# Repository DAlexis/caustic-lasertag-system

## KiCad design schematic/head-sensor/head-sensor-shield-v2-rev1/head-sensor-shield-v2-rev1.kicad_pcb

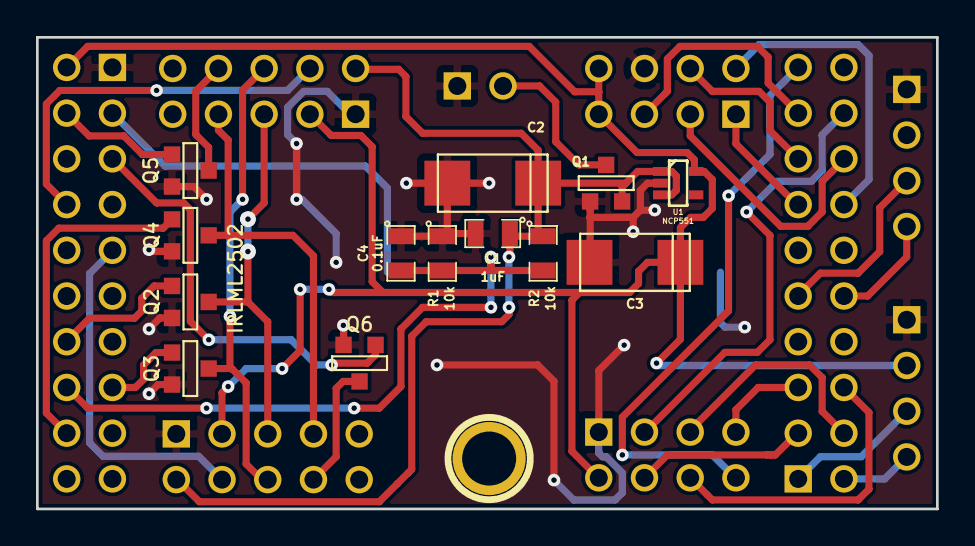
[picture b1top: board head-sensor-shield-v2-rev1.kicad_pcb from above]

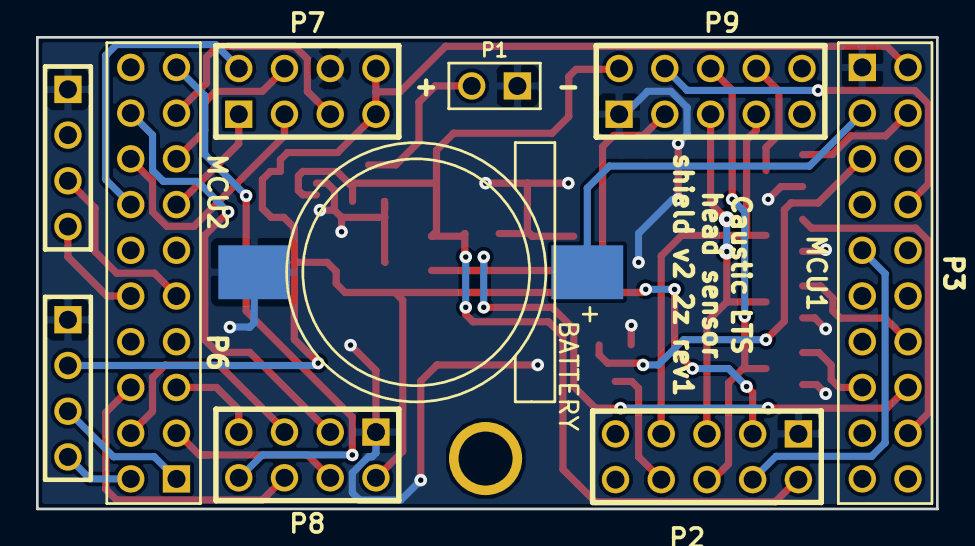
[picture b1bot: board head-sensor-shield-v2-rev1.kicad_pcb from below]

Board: 2 copper layers, 50.0 x 26.2 mm, 23 parts (10 on the bottom side), 33 nets.

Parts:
+: BATTERY; CR1220-smd
C1: 1uF; SM0805
C2, C3: 100uF; c_tant_C
C4: 0.1uF; SM0805
P1: Power_in; PIN_ARRAY_2X1
P2: Zone2; PIN_ARRAY_5x2
P3: MCU1; pin_array_10x2
P4: UART1; PIN_ARRAY_4x1
P5: UART3; PIN_ARRAY_4x1
P6: MCU2; pin_array_10x2
P7: RFID; pin_array_4x2
P8: NRF24L01; pin_array_4x2
P9: Zone1; PIN_ARRAY_5x2
Q1, Q2, Q3, Q4, Q6: SOT23GDS
Q5: IRLML2502; SOT23GDS
R1, R2: 10k; SM0805
U1: NCP551; sot323-5-fx

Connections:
+3.3V: C3.1, P2.3, P3.2, P5.2, P7.7, P7.8, P8.2, P9.3, U1.5
+BATT: +.1, P3.3
GND: +.2, C1.2, C2.2, C3.2, C4.1, P1.1, P2.1, P3.1, P4.1, P5.1, P7.6, P8.1, P9.1, Q1.G, Q2.S, Q3.S, Q4.S, Q5.S, Q6.S, R1.1, U1.2
unnamed: P3.18, Q4.G
unnamed: P3.15, Q3.G
unnamed: P3.5, Q6.G
unnamed: P5.4, P6.2
unnamed: P2.7, P9.7, Q4.D
unnamed: P3.14, Q2.G
unnamed: P1.2, Q1.D
unnamed: P6.19, P8.8
unnamed: P6.18, P8.3
unnamed: P6.3, P8.4
unnamed: P6.4, P8.5
unnamed: P6.6, P8.6
unnamed: P6.5, P8.7
unnamed: P6.13, P7.1
unnamed: P5.3, P6.1
unnamed: P2.8, Q6.D
unnamed: C4.2, P3.16, R1.2, R2.2
unnamed: P2.4, P3.9
unnamed: P3.8, P9.4
unnamed: P4.4, P6.10
unnamed: P4.3, P6.9
unnamed: P3.4, Q5.G
unnamed: P9.8, Q5.D
unnamed: P2.5, P9.5, Q2.D
unnamed: P2.6, P9.6, Q3.D
unnamed: P6.14, P7.2
unnamed: P6.17, P7.5
unnamed: P6.16, P7.3
unnamed: P6.15, P7.4
VCC: C1.1, C2.1, P2.2, P9.2, Q1.S, R2.1, U1.1, U1.3

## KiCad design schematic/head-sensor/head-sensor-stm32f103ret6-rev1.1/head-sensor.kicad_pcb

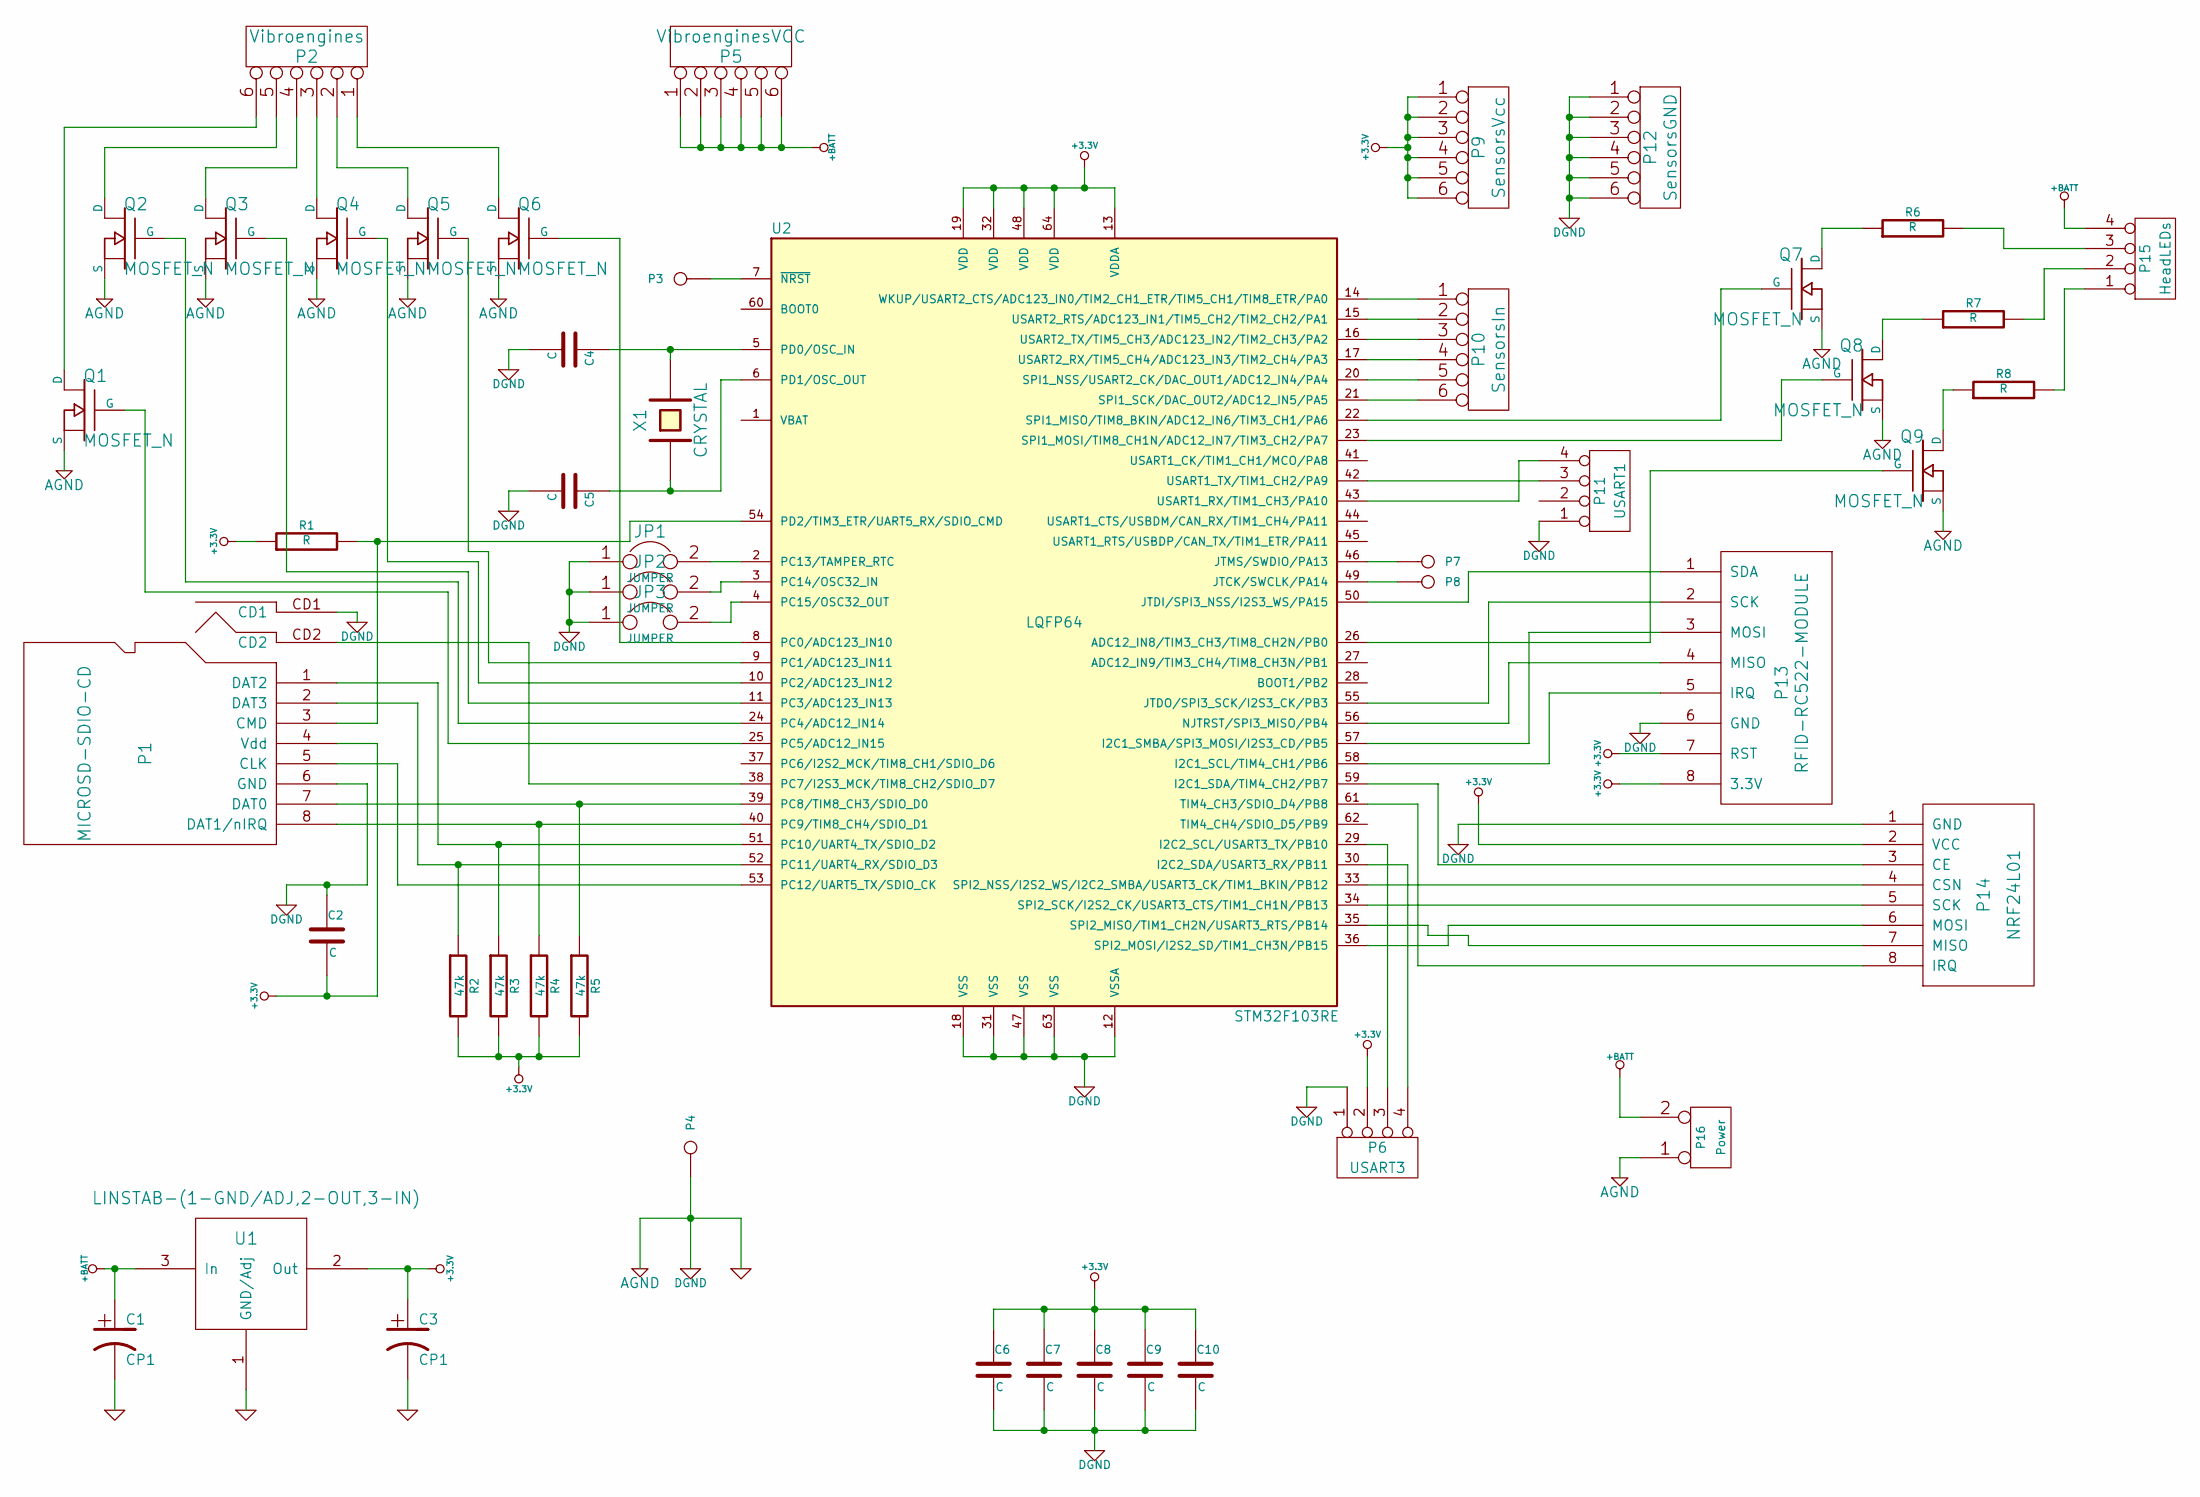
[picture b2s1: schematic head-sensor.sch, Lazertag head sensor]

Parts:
C1, C3: CP1
C2, C4, C5, C6, C7, C8, C9, C10: C
JP1, JP2, JP3: JUMPER
P1: MICROSD-SDIO-CD
P2: Vibroengines
P3: NRST
P4: SWGND
P5: VibroenginesVCC
P6: USART3
P7: SWDIO
P8: SWCLK
P9: SensorsVcc
P10: SensorsIn
P11: USART1
P12: SensorsGND
P13: RFID-RC522-MODULE
P14: NRF24L01
P15: HeadLEDs
P16: Power
Q1, Q2, Q3, Q4, Q5, Q6, Q7, Q8, Q9: MOSFET_N
R1, R6, R7, R8: R
R2, R3, R4, R5: 47k
U1: LINSTAB-(1-GND/ADJ,2-OUT,3-IN)
U2: STM32F103RE; LQFP64
X1: CRYSTAL

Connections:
+3.3V: C2.2, C3.1, C6.1, C7.1, C8.1, C9.1, C10.1, P1.4 (Vdd), P6.2, P9.1, P9.2, P9.3, P9.4, P9.5, P9.6, P13.7 (RST), P13.8 (3.3V), P14.2 (VCC), R1.1, R2.2, R3.2, R4.2, R5.2, U1.2 (Out), U2.13 (VDDA), U2.19 (VDD), U2.32 (VDD), U2.48 (VDD), U2.64 (VDD)
+BATT: C1.1, P5.1, P5.2, P5.3, P5.4, P5.5, P5.6, P15.4, P16.2 (PM), U1.3 (In)
AGND: C1.2, C2.1, C3.2, C4.2, C5.2, C6.2, C7.2, C8.2, C9.2, C10.2, JP1.1, JP2.1, JP3.1, P1.6 (GND), P1.CD1, P4.1, P6.1, P11.1, P12.1, P12.2, P12.3, P12.4, P12.5, P12.6, P13.6 (GND), P14.1 (GND), P16.1, Q1.S, Q2.S, Q3.S, Q4.S, Q5.S, Q6.S, Q7.S, Q8.S, Q9.S, U1.1 (GND/Adj), U2.12 (VSSA), U2.18 (VSS), U2.31 (VSS), U2.47 (VSS), U2.63 (VSS)
unnamed: Q8.D, R7.1
unnamed: Q7.D, R6.1
unnamed: P15.2, R7.2
unnamed: P15.3, R6.2
unnamed: P2.6, Q1.D
unnamed: P1.8 (DAT1/nIRQ), R4.1, U2.40 (PC9/TIM8_CH4/SDIO_D1)
unnamed: P1.7 (DAT0), R5.1, U2.39 (PC8/TIM8_CH3/SDIO_D0)
unnamed: P2.5, Q2.D
unnamed: Q9.D, R8.1
unnamed: P15.1, R8.2
unnamed: Q4.G, U2.10 (PC2/ADC123_IN12)
unnamed: Q2.G, U2.24 (PC4/ADC12_IN14)
unnamed: Q3.G, U2.11 (PC3/ADC123_IN13)
unnamed: Q5.G, U2.9 (PC1/ADC123_IN11)
unnamed: Q6.G, U2.8 (PC0/ADC123_IN10)
unnamed: P2.1, Q6.D
unnamed: P2.4, Q3.D
unnamed: P2.3, Q4.D
unnamed: P2.2, Q5.D
unnamed: Q1.G, U2.25 (PC5/ADC12_IN15)
unnamed: P13.5 (IRQ), U2.58 (I2C1_SCL/TIM4_CH1/PB6)
unnamed: P13.4 (MISO), U2.56 (NJTRST/SPI3_MISO/PB4)
unnamed: P13.3 (MOSI), U2.57 (I2C1_SMBA/SPI3_MOSI/I2S3_CD/PB5)
unnamed: P6.3, U2.29 (I2C2_SCL/USART3_TX/PB10)
unnamed: P6.4, U2.30 (I2C2_SDA/USART3_RX/PB11)
unnamed: P7.1, U2.46 (JTMS/SWDIO/PA13)
unnamed: P14.3 (CE), U2.59 (I2C1_SDA/TIM4_CH2/PB7)
unnamed: P14.8 (IRQ), U2.61 (TIM4_CH3/SDIO_D4/PB8)
unnamed: P3.1, U2.7 (~NRST)
unnamed: P8.1, U2.49 (JTCK/SWCLK/PA14)
unnamed: P13.1 (SDA), U2.50 (JTDI/SPI3_NSS/I2S3_WS/PA15)
unnamed: P13.2 (SCK), U2.55 (JTDO/SPI3_SCK/I2S3_CK/PB3)
unnamed: P1.5 (CLK), U2.53 (PC12/UART5_TX/SDIO_CK)
unnamed: P1.1 (DAT2), R3.1, U2.51 (PC10/UART4_TX/SDIO_D2)
unnamed: P1.3 (CMD), R1.2, U2.54 (PD2/TIM3_ETR/UART5_RX/SDIO_CMD)
unnamed: P1.2 (DAT3), R2.1, U2.52 (PC11/UART4_RX/SDIO_D3)
unnamed: Q8.G, U2.23 (SPI1_MOSI/TIM8_CH1N/ADC12_IN7/TIM3_CH2/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)
unnamed: P10.1, U2.14 (WKUP/USART2_CTS/ADC123_IN0/TIM2_CH1_ETR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)
unnamed: P10.2, U2.15 (USART2_RTS/ADC123_IN1/TIM5_CH2/TIM2_CH2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)
unnamed: P10.3, U2.16 (USART2_TX/TIM5_CH3/ADC123_IN2/TIM2_CH3/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)
unnamed: P10.4, U2.17 (USART2_RX/TIM5_CH4/ADC123_IN3/TIM2_CH4/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)
unnamed: P10.5, U2.20 (SPI1_NSS/USART2_CK/DAC_OUT1/ADC12_IN4/P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)
unnamed: P10.6, U2.21 (SPI1_SCK/DAC_OUT2/ADC12_IN5/PA5)
unnamed: Q7.G, U2.22 (SPI1_MISO/TIM8_BKIN/ADC12_IN6/TIM3_CH1/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)
unnamed: Q9.G, U2.26 (ADC12_IN8/TIM3_CH3/TIM8_CH2N/PB0)
unnamed: JP3.2, U2.4 (PC15/OSC32_OUT)
unnamed: JP1.2, U2.2 (PC13/TAMPER_RTC)
unnamed: JP2.2, U2.3 (PC14/OSC32_IN)
unnamed: P1.CD2, U2.38 (PC7/I2S3_MCK/TIM8_CH2/SDIO_D7)
unnamed: C4.1, U2.5 (PD0/OSC_IN), X1.2
unnamed: C5.1, U2.6 (PD1/OSC_OUT), X1.1
unnamed: P14.4 (CSN), U2.33 (SPI2_NSS/I2S2_WS/I2C2_SMBA/USART3_CK/TI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)
unnamed: P11.3, U2.42 (USART1_TX/TIM1_CH2/PA9)
unnamed: P14.5 (SCK), U2.34 (SPI2_SCK/I2S2_CK/USART3_CTS/TIM1_CH1N/P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)
unnamed: P11.4, U2.43 (USART1_RX/TIM1_CH3/PA10)
unnamed: P14.7 (MISO), U2.35 (SPI2_MISO/TIM1_CH2N/USART3_RTS/PB14)
unnamed: P14.6 (MOSI), U2.36 (SPI2_MOSI/I2S2_SD/TIM1_CH3N/PB15)

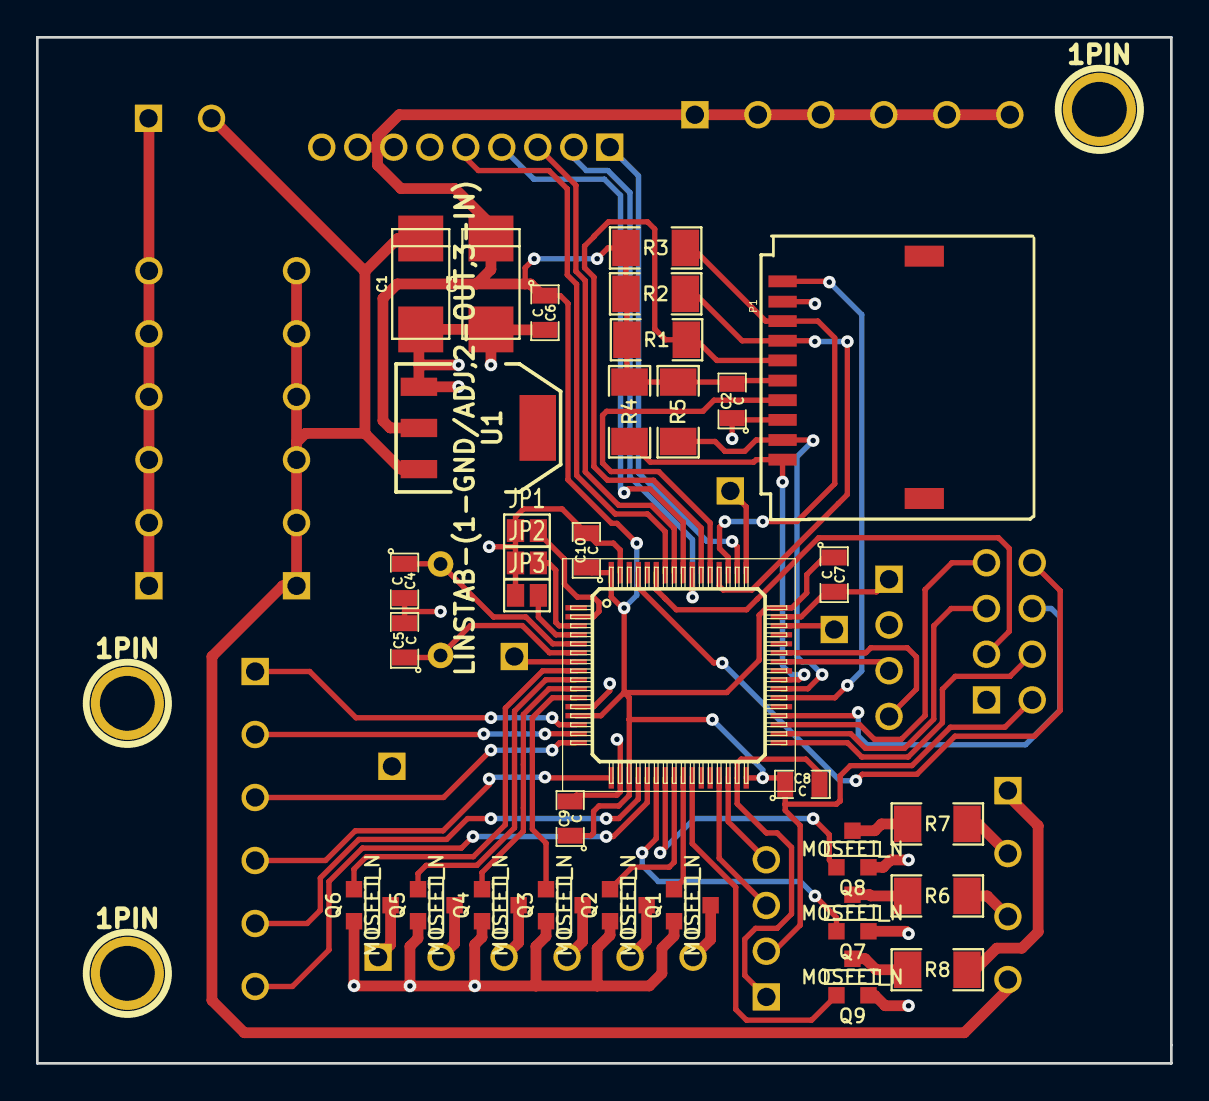
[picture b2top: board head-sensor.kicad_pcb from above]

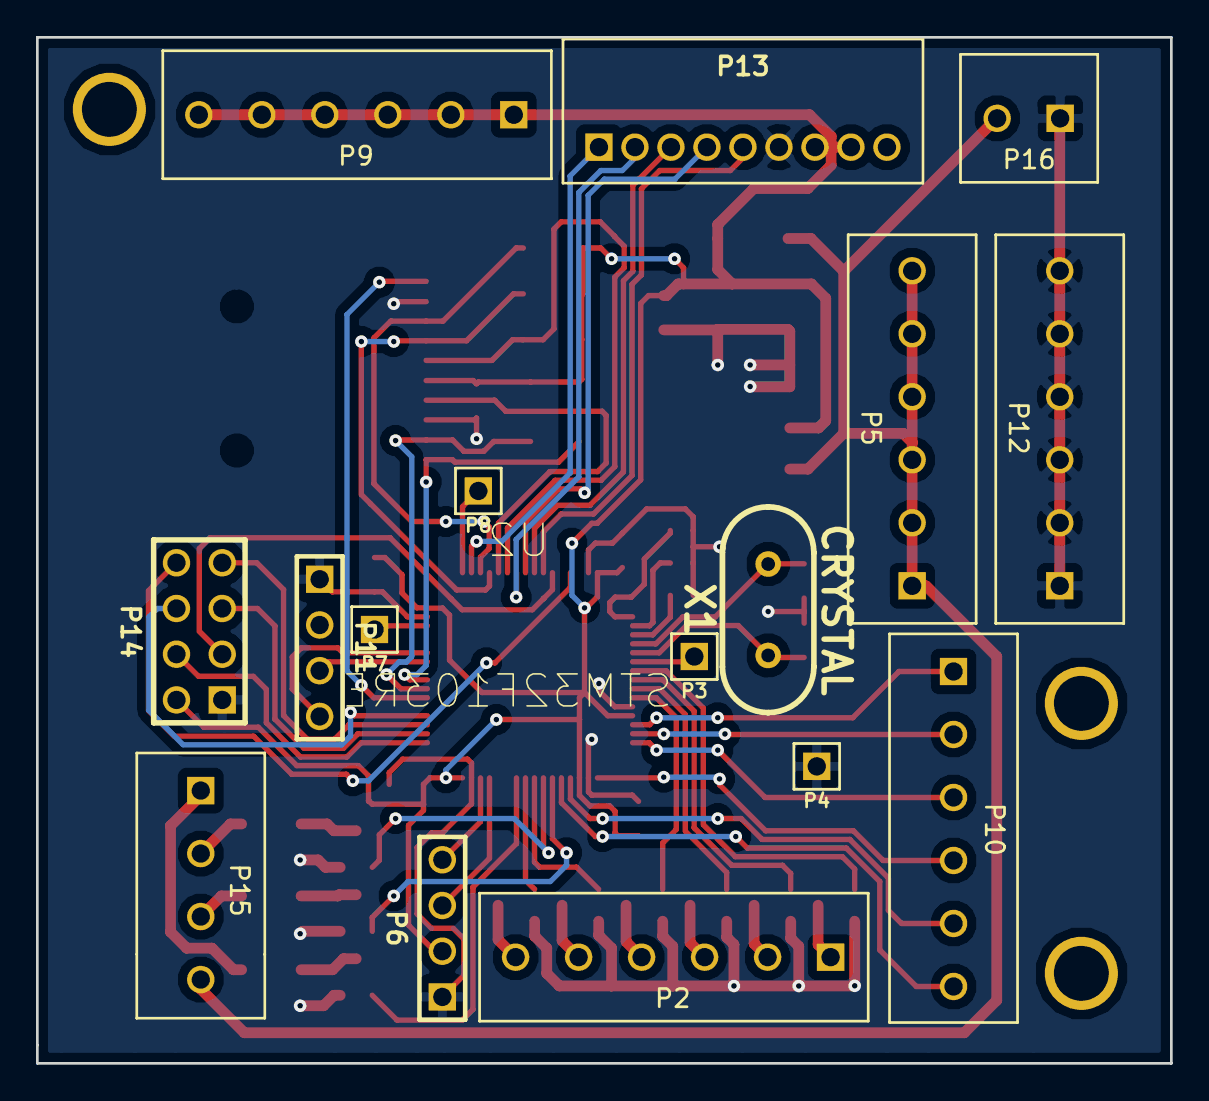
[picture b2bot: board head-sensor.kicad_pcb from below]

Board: 2 copper layers, 63.0 x 57.0 mm, 52 parts (16 on the bottom side), 60 nets.

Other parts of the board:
1PIN, 1PIN#2, 1PIN#3: P***; 1pin

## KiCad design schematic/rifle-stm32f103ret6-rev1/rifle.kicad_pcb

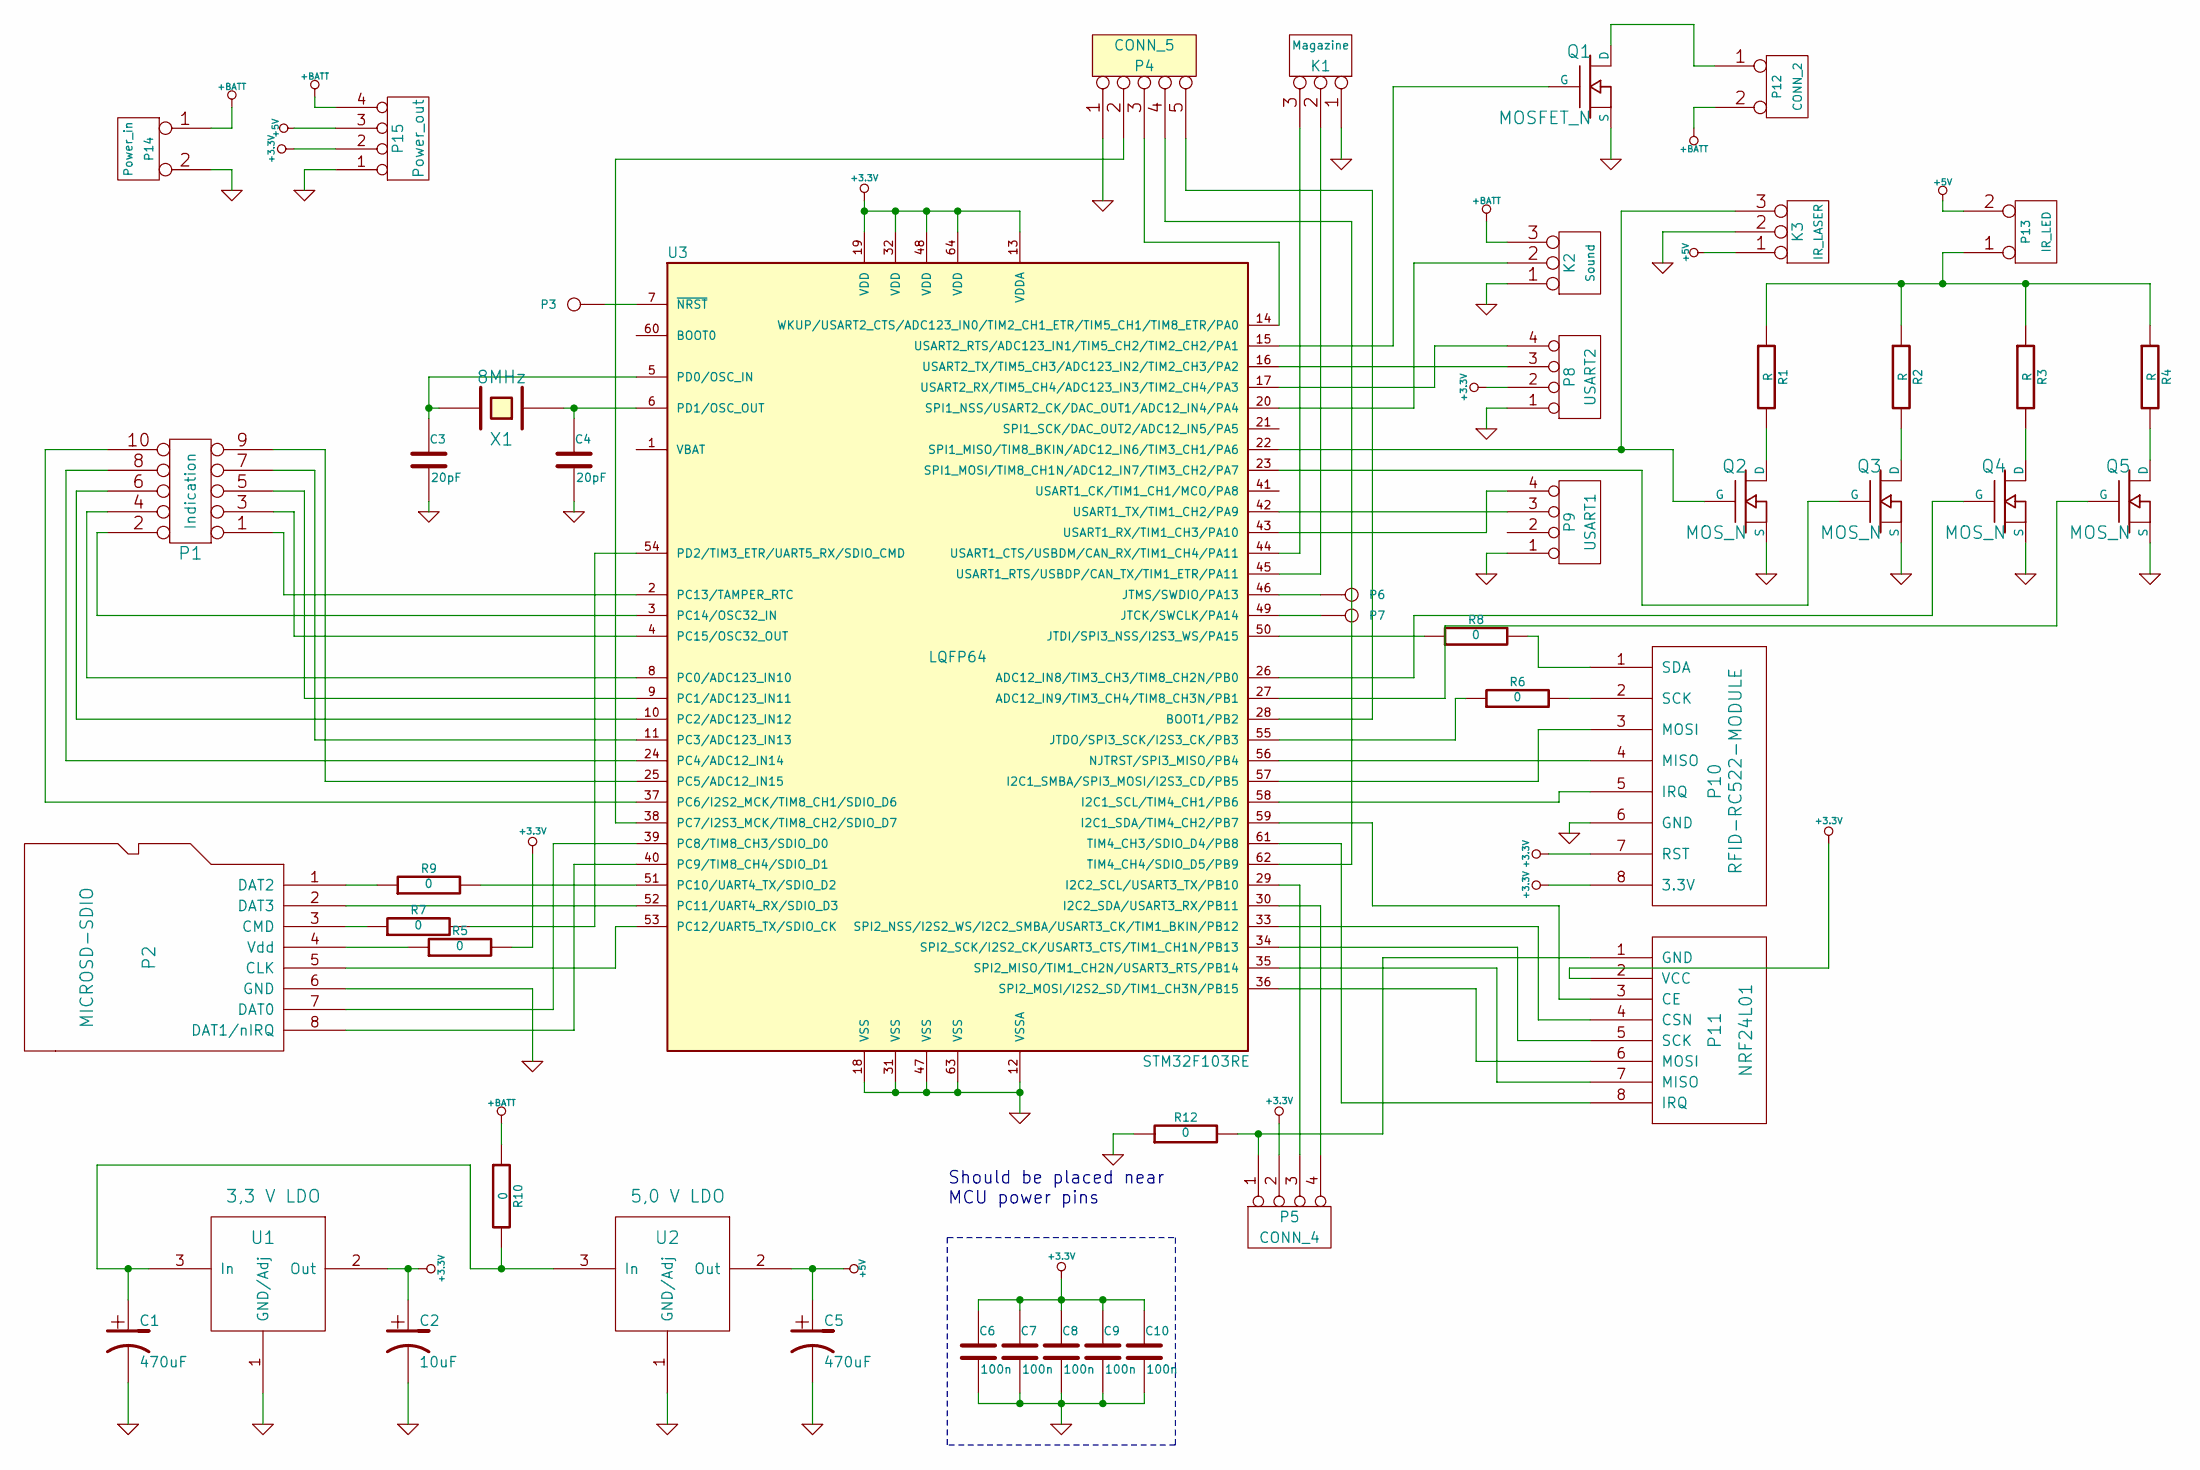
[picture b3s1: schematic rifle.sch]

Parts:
C1, C5: 470uF
C2: 10uF
C3, C4: 20pF
C6, C7, C8, C9, C10: 100n
K1: Magazine
K2: Sound
K3: IR_LASER
P1: Indication
P2: MICROSD-SDIO
P3: Reset
P4: CONN_5
P5: CONN_4
P6: SWD_IO
P7: SWD_CLK
P8: USART2
P9: USART1
P10: RFID-RC522-MODULE
P11: NRF24L01
P12: CONN_2
P13: IR_LED
P14: Power_in
P15: Power_out
Q1: MOSFET_N
Q2, Q3, Q4, Q5: MOS_N
R1, R2, R3, R4: R
R5, R6, R7, R8, R9, R10, R12: 0
U1: 3,3 V LDO
U2: 5,0 V LDO
U3: STM32F103RE; LQFP64
X1: 8MHz

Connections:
+3.3V: C2.1, C6.1, C7.1, C8.1, C9.1, C10.1, P5.2, P8.2, P10.7 (RST), P10.8 (3.3V), P11.2 (VCC), P15.2, R5.2, U1.2 (Out), U3.13 (VDDA), U3.19 (VDD), U3.32 (VDD), U3.48 (VDD), U3.64 (VDD)
+5V: C5.1, K3.1, P13.2 (PM), P15.3, U2.2 (Out)
+BATT: K2.3, P12.2 (PM), P14.1, P15.4, R10.1
GND: C1.2, C2.2, C3.2, C4.2, C5.2, C6.2, C7.2, C8.2, C9.2, C10.2, K1.1, K2.1, K3.2 (PM), P2.6 (GND), P4.1, P8.1, P9.1, P10.6 (GND), P14.2 (PM), P15.1, Q1.S, Q2.S, Q3.S, Q4.S, Q5.S, R12.1, U1.1 (GND/Adj), U2.1 (GND/Adj), U3.12 (VSSA), U3.18 (VSS), U3.31 (VSS), U3.47 (VSS), U3.63 (VSS)
unnamed: P11.6 (MOSI), U3.36 (SPI2_MOSI/I2S2_SD/TIM1_CH3N/PB15)
unnamed: P11.7 (MISO), U3.35 (SPI2_MISO/TIM1_CH2N/USART3_RTS/PB14)
unnamed: P11.5 (SCK), U3.34 (SPI2_SCK/I2S2_CK/USART3_CTS/TIM1_CH1N/P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)
unnamed: P11.4 (CSN), U3.33 (SPI2_NSS/I2S2_WS/I2C2_SMBA/USART3_CK/TI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)
unnamed: P11.8 (IRQ), U3.61 (TIM4_CH3/SDIO_D4/PB8)
unnamed: P11.3 (CE), U3.59 (I2C1_SDA/TIM4_CH2/PB7)
unnamed: P10.5 (IRQ), U3.58 (I2C1_SCL/TIM4_CH1/PB6)
unnamed: P10.3 (MOSI), U3.57 (I2C1_SMBA/SPI3_MOSI/I2S3_CD/PB5)
unnamed: P10.1 (SDA), R8.2
unnamed: P5.3, U3.29 (I2C2_SCL/USART3_TX/PB10)
unnamed: P5.4, U3.30 (I2C2_SDA/USART3_RX/PB11)
unnamed: Q3.G, U3.23 (SPI1_MOSI/TIM8_CH1N/ADC12_IN7/TIM3_CH2/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)
unnamed: Q4.G, U3.26 (ADC12_IN8/TIM3_CH3/TIM8_CH2N/PB0)
unnamed: Q5.G, U3.27 (ADC12_IN9/TIM3_CH4/TIM8_CH3N/PB1)
unnamed: P13.1, R1.1, R2.1, R3.1, R4.1
unnamed: Q2.D, R1.2
unnamed: Q3.D, R2.2
unnamed: Q4.D, R3.2
unnamed: Q5.D, R4.2
unnamed: C3.1, U3.5 (PD0/OSC_IN), X1.2
unnamed: C4.1, U3.6 (PD1/OSC_OUT), X1.1
unnamed: P6.1, U3.46 (JTMS/SWDIO/PA13)
unnamed: P7.1, U3.49 (JTCK/SWCLK/PA14)
unnamed: P3.1, U3.7 (~NRST)
unnamed: P9.3, U3.42 (USART1_TX/TIM1_CH2/PA9)
unnamed: P9.4, U3.43 (USART1_RX/TIM1_CH3/PA10)
unnamed: P8.3, U3.16 (USART2_TX/TIM5_CH3/ADC123_IN2/TIM2_CH3/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)
unnamed: P8.4, U3.17 (USART2_RX/TIM5_CH4/ADC123_IN3/TIM2_CH4/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)
unnamed: P10.4 (MISO), U3.56 (NJTRST/SPI3_MISO/PB4)
unnamed: P4.5, U3.28 (BOOT1/PB2)
unnamed: P10.2 (SCK), R6.2
unnamed: R6.1, U3.55 (JTDO/SPI3_SCK/I2S3_CK/PB3)
unnamed: P4.2, U3.38 (PC7/I2S3_MCK/TIM8_CH2/SDIO_D7)
unnamed: P12.1, Q1.D
unnamed: P4.3, U3.14 (WKUP/USART2_CTS/ADC123_IN0/TIM2_CH1_ETR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)
unnamed: P4.4, U3.62 (TIM4_CH4/SDIO_D5/PB9)
unnamed: P5.1, P11.1 (GND), R12.2
unnamed: P2.4 (Vdd), R5.1
unnamed: P2.1 (DAT2), R9.1
unnamed: R9.2, U3.51 (PC10/UART4_TX/SDIO_D2)
unnamed: P2.3 (CMD), R7.1
unnamed: R8.1, U3.50 (JTDI/SPI3_NSS/I2S3_WS/PA15)
unnamed: C1.1, R10.2, U1.3 (In), U2.3 (In)
unnamed: P1.7, U3.11 (PC3/ADC123_IN13)
unnamed: P1.4, U3.8 (PC0/ADC123_IN10)
unnamed: P1.5, U3.9 (PC1/ADC123_IN11)
unnamed: P1.6, U3.10 (PC2/ADC123_IN12)
unnamed: P2.2 (DAT3), U3.52 (PC11/UART4_RX/SDIO_D3)
unnamed: P2.5 (CLK), U3.53 (PC12/UART5_TX/SDIO_CK)
unnamed: R7.2, U3.54 (PD2/TIM3_ETR/UART5_RX/SDIO_CMD)
unnamed: P1.1, U3.2 (PC13/TAMPER_RTC)
unnamed: K3.3, Q2.G, U3.22 (SPI1_MISO/TIM8_BKIN/ADC12_IN6/TIM3_CH1/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)
unnamed: P1.2, U3.3 (PC14/OSC32_IN)
unnamed: P1.3, U3.4 (PC15/OSC32_OUT)
unnamed: P1.10, U3.37 (PC6/I2S2_MCK/TIM8_CH1/SDIO_D6)
unnamed: K2.2 (PM), U3.20 (SPI1_NSS/USART2_CK/DAC_OUT1/ADC12_IN4/P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)
unnamed: K1.3, U3.44 (USART1_CTS/USBDM/CAN_RX/TIM1_CH4/PA11)
unnamed: K1.2 (PM), U3.45 (USART1_RTS/USBDP/CAN_TX/TIM1_ETR/PA11)
unnamed: P1.8, U3.24 (PC4/ADC12_IN14)
unnamed: P1.9, U3.25 (PC5/ADC12_IN15)

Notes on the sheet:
Should be placed near MCU power pins

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
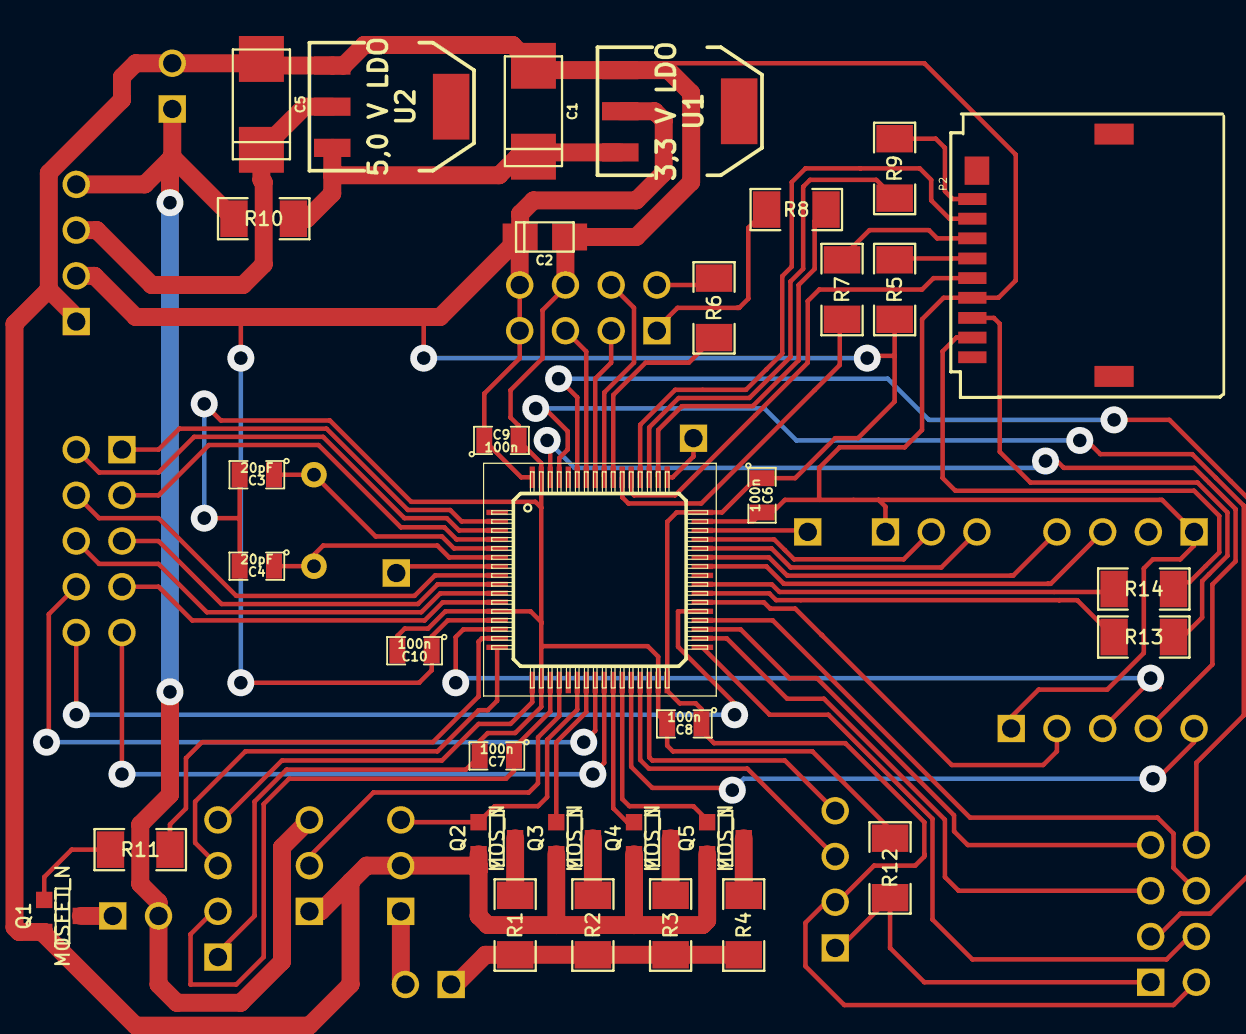
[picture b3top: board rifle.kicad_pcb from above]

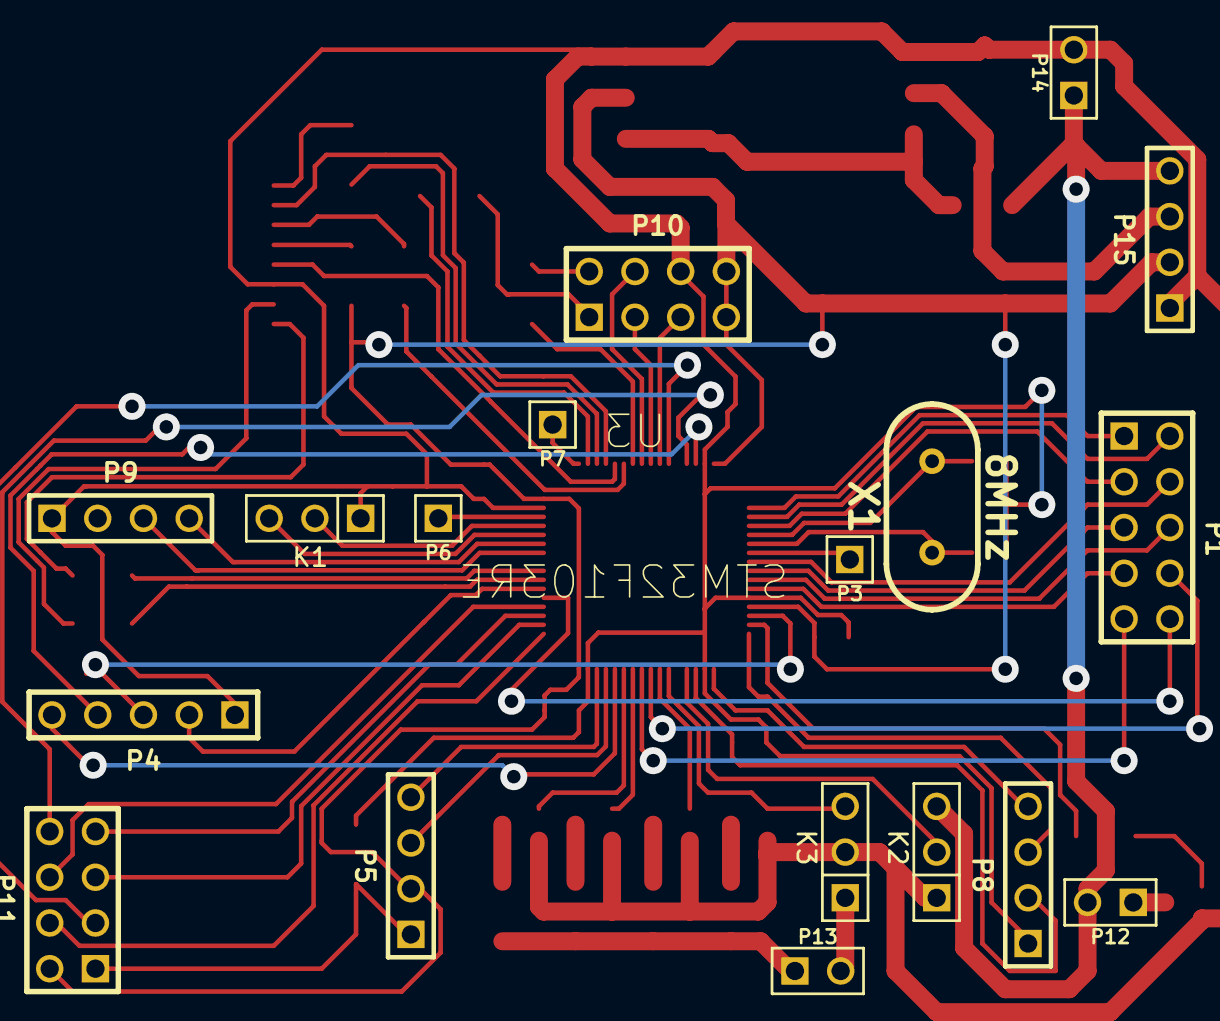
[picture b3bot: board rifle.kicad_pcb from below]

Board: 2 copper layers, 51 parts (18 on the bottom side), 70 nets.

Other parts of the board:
R11, R13, R14: 0; SM1206

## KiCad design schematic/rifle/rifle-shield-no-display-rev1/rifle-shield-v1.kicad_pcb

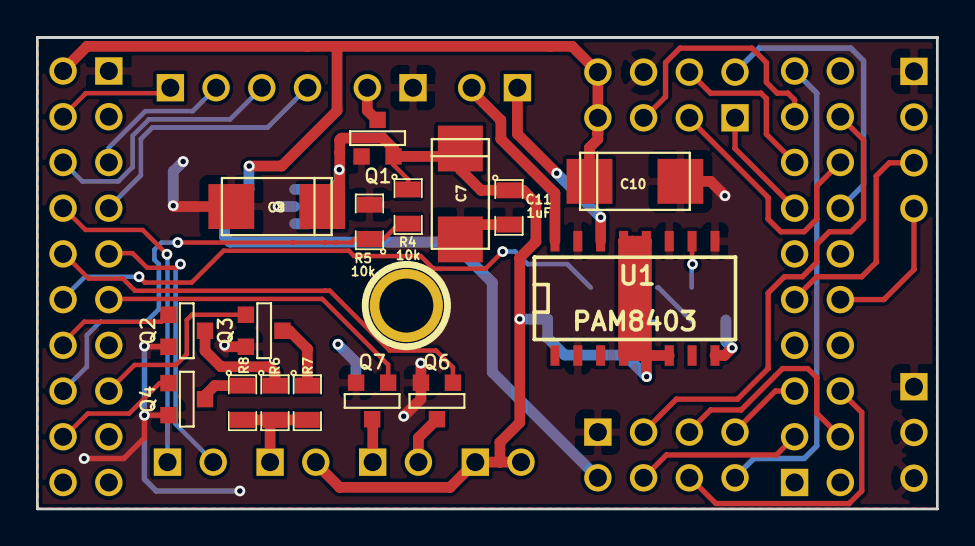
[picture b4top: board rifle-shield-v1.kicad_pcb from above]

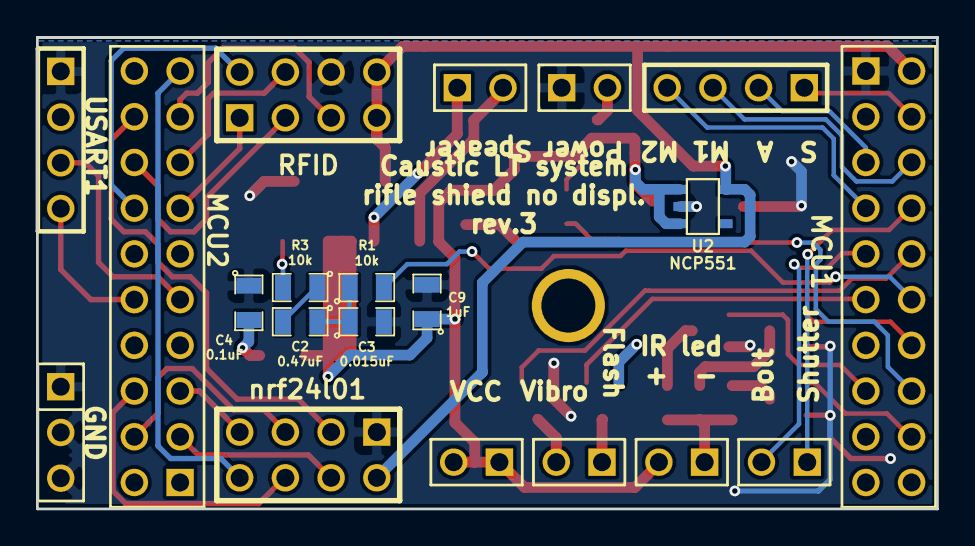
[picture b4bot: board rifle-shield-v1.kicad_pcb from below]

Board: 2 copper layers, 50.0 x 26.2 mm, 36 parts (20 on the bottom side), 42 nets.

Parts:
C2: 0.47uF; SM0805
C3: 0.015uF; SM0805
C4: 0.1uF; SM0805
C7, C10: CP1; c_tant_C
C8: 470uF; c_tant_C
C9, C11: 1uF; SM0805
K1: CONN_3; PIN_ARRAY_3X1
P1: Power; PIN_ARRAY_2X1
P2: MCU1; pin_array_10x2
P3: Mag&fireMode; PIN_ARRAY_4x1
P4: VCC; PIN_ARRAY_2X1
P5: Speaker2; PIN_ARRAY_2X1
P6: USART1; PIN_ARRAY_4x1
P7: Fire&Reload; PIN_ARRAY_2X1
P10: MCU2; pin_array_10x2
P15: Vibro&flash; PIN_ARRAY_2X1
Q1, Q2, Q3, Q4: SOT23GDS
Q6, Q7: MOS_N; SOT23GDS
R1, R3, R4, R5: 10k; SM0805
R6, R7, R8: SM0805
RFID: RFID-RC522-MODULE; pin_array_4x2
U1: PAM8403; SO16N
U2: NCP551; SOT23-5
e: IR_LED; PIN_ARRAY_2X1
nrf24l01: NRF24L01; pin_array_4x2

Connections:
+3.3V: C10.1, P2.2, RFID.7, RFID.8, U2.5, nrf24l01.2
GND: C3.2, C4.1, C7.2, C8.2, C9.2, C10.2, C11.2, K1.1, K1.2, K1.3, P1.1, P2.1, P6.1, Q1.G, Q2.S, Q3.S, Q4.S, Q6.S, Q7.S, R5.2, RFID.6, U1.2, U1.9, U1.11, U1.15, U2.2, nrf24l01.1
unnamed: C4.2, U1.8
unnamed: P2.5, P3.2
unnamed: P2.12, R1.2
unnamed: C2.1, C3.1, R1.1
unnamed: P2.8, P7.1
unnamed: P2.9, P7.2
unnamed: P2.7, P3.4
unnamed: P2.6, P3.3
unnamed: P2.4, P3.1
unnamed: P5.2, U1.16
unnamed: P5.1, U1.14
unnamed: C2.2, R3.1
unnamed: R3.2, U1.10
unnamed: P10.13, RFID.1
unnamed: P10.6, nrf24l01.6
unnamed: P10.5, nrf24l01.7
unnamed: P10.17, RFID.5
unnamed: P10.14, RFID.2
unnamed: P10.16, RFID.3
unnamed: P10.15, RFID.4
unnamed: P10.19, nrf24l01.8
unnamed: P10.18, nrf24l01.3
unnamed: P10.3, nrf24l01.4
unnamed: P10.4, nrf24l01.5
unnamed: P6.4, P10.10
unnamed: P6.3, P10.9
unnamed: P2.16, R4.2, R5.1
unnamed: P2.11, Q7.G
unnamed: P2.10, Q6.G
unnamed: P2.15, Q3.G
unnamed: P2.14, Q2.G
unnamed: R6.2, R7.2, R8.2, e.1
unnamed: Q4.D, R8.1
unnamed: Q3.D, R7.1
unnamed: Q2.D, R6.1
unnamed: P15.1, Q7.D
unnamed: P15.2, Q6.D
unnamed: P1.2, Q1.D
unnamed: P2.18, Q4.G
VCC: C7.1, C8.1, C9.1, C11.1, P4.1, P4.2, Q1.S, R4.1, U1.4, U1.5, U1.6, U1.12, U1.13, U2.1, U2.3, e.2
